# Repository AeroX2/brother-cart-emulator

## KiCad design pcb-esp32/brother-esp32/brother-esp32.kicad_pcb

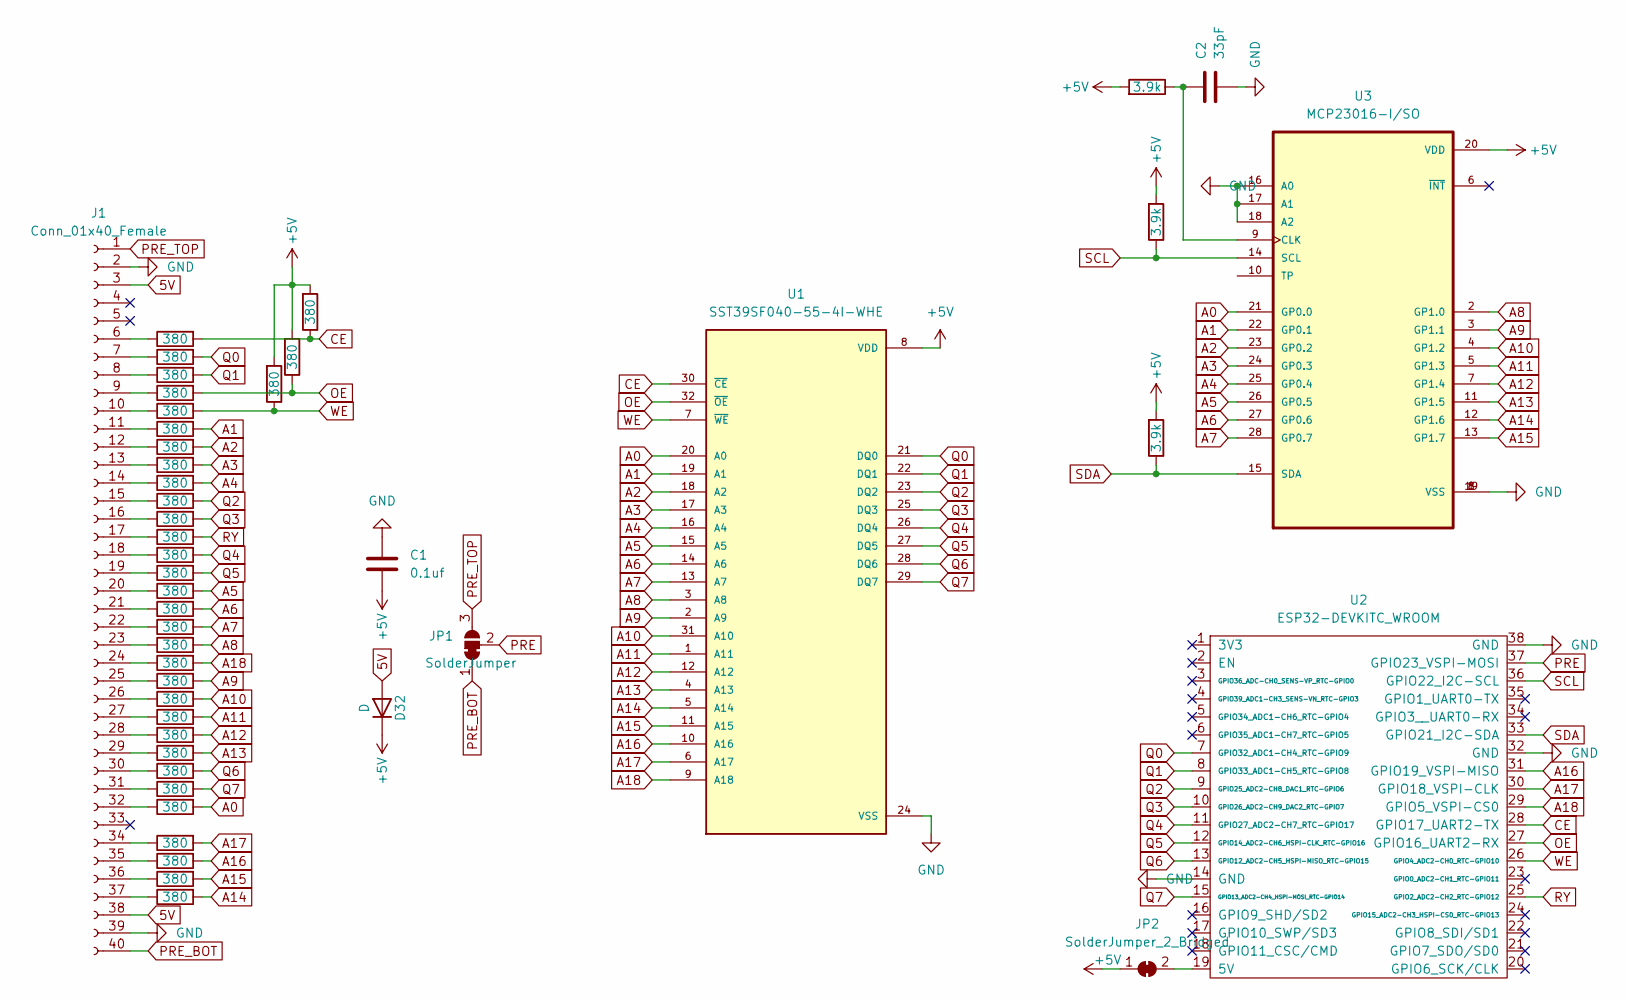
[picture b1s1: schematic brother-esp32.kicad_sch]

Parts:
C1: 0.1uf; C_0603_1608Metric_Pad1.08x0.95mm_HandSolder
C2: 33pF; C_0603_1608Metric_Pad1.08x0.95mm_HandSolder
D32: D; D_SOD-323_HandSoldering
J1: Conn_01x40_Female; PinHeader_1x40_SMD
JP1: SolderJumper; SolderJumper-3_P1.3mm_Bridged12_Pad1.0x1.5mm
JP2: SolderJumper_2_Bridged; SolderJumper-2_P1.3mm_Bridged_RoundedPad1.0x1.5mm
R1, R2, R3, R4, R5, R6, R7, R8, R9, R10, R11, R12, R13, R14, R15, R16, R17, R18, R19, R20, R21, R22, R23, R24, R25, R26, R27, R28, R29, R30, R31, R32, R33, R34: 380; R_0603_1608Metric_Pad0.98x0.95mm_HandSolder
R35, R36, R37: 3.9k; R_0603_1608Metric_Pad0.98x0.95mm_HandSolder
U1: SST39SF040-55-4I-WHE; SOP50P1400X120-32N; PARTREV C
U2: ESP32-DEVKITC_WROOM; ESP32-DOIT-DEVKIT
U3: MCP23016-I/SO; SOIC127P1030X265-28N

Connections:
5V: D32.2 (A), J1.3, J1.38
+5V: C1.2, D32.1 (K), JP2.1 (A), R32.2, R33.2, R34.2, R35.2, R36.2, R37.2, U1.8 (VDD), U3.20 (VDD)
A0: R27.2, U1.20 (A0), U3.21 (GP0.0)
A1: R6.2, U1.19 (A1), U3.22 (GP0.1)
A2: R7.2, U1.18 (A2), U3.23 (GP0.2)
A3: R8.2, U1.17 (A3), U3.24 (GP0.3)
A4: R9.2, U1.16 (A4), U3.25 (GP0.4)
A5: R15.2, U1.15 (A5), U3.26 (GP0.5)
A6: R16.2, U1.14 (A6), U3.27 (GP0.6)
A7: R17.2, U1.13 (A7), U3.28 (GP0.7)
A8: R18.2, U1.3 (A8), U3.2 (GP1.0)
A9: R20.2, U1.2 (A9), U3.3 (GP1.1)
A10: R21.2, U1.31 (A10), U3.4 (GP1.2)
A11: R22.2, U1.1 (A11), U3.5 (GP1.3)
A12: R23.2, U1.12 (A12), U3.7 (GP1.4)
A13: R24.2, U1.4 (A13), U3.11 (GP1.5)
A14: R31.2, U1.5 (A14), U3.12 (GP1.6)
A15: R30.2, U1.11 (A15), U3.13 (GP1.7)
A16: R29.2, U1.10 (A16), U2.31 (GPIO19_VSPI-MISO)
A17: R28.2, U1.6 (A17), U2.30 (GPIO18_VSPI-CLK)
A18: R19.2, U1.9 (A18), U2.29 (GPIO5_VSPI-CS0)
CE: R1.2, R34.1, U1.30 (~CE), U2.28 (GPIO17_UART2-TX)
GND: C1.1, C2.2, J1.2, J1.39, U1.24 (VSS), U2.14 (GND), U2.32 (GND), U2.38 (GND), U3.1 (VSS), U3.8 (VSS), U3.16 (A0), U3.17 (A1), U3.18 (A2), U3.19 (VSS)
unnamed: C2.1, R35.1, U3.9 (CLK)
unnamed: J1.6, R1.1
unnamed: J1.7, R2.1
unnamed: J1.8, R3.1
unnamed: J1.9, R4.1
unnamed: J1.10, R5.1
unnamed: J1.11, R6.1
unnamed: J1.12, R7.1
unnamed: J1.13, R8.1
unnamed: J1.14, R9.1
unnamed: J1.15, R10.1
unnamed: J1.16, R11.1
unnamed: J1.17, R12.1
unnamed: J1.18, R13.1
unnamed: J1.19, R14.1
unnamed: J1.20, R15.1
unnamed: J1.21, R16.1
unnamed: J1.22, R17.1
unnamed: J1.23, R18.1
unnamed: J1.24, R19.1
unnamed: J1.25, R20.1
unnamed: J1.26, R21.1
unnamed: J1.27, R22.1
unnamed: J1.28, R23.1
unnamed: J1.29, R24.1
unnamed: J1.30, R25.1
unnamed: J1.31, R26.1
unnamed: J1.32, R27.1
unnamed: J1.34, R28.1
unnamed: J1.35, R29.1
unnamed: J1.36, R30.1
unnamed: J1.37, R31.1
unnamed: JP2.2 (B), U2.19 (5V)
OE: R4.2, R33.1, U1.32 (~OE), U2.27 (GPIO16_UART2-RX)
PRE: JP1.2 (C), U2.37 (GPIO23_VSPI-MOSI)
PRE_BOT: J1.40, JP1.1 (A)
PRE_TOP: J1.1, JP1.3 (B)
Q0: R2.2, U1.21 (DQ0), U2.7 (GPIO32_ADC1-CH4_RTC-GPIO9)
Q1: R3.2, U1.22 (DQ1), U2.8 (GPIO33_ADC1-CH5_RTC-GPIO8)
Q2: R10.2, U1.23 (DQ2), U2.9 (GPIO25_ADC2-CH8_DAC1_RTC-GPIO6)
Q3: R11.2, U1.25 (DQ3), U2.10 (GPIO26_ADC2-CH9_DAC2_RTC-GPIO7)
Q4: R13.2, U1.26 (DQ4), U2.11 (GPIO27_ADC2-CH7_RTC-GPIO17)
Q5: R14.2, U1.27 (DQ5), U2.12 (GPIO14_ADC2-CH6_HSPI-CLK_RTC-GPIO16)
Q6: R25.2, U1.28 (DQ6), U2.13 (GPIO12_ADC2-CH5_HSPI-MISO_RTC-GPIO15)
Q7: R26.2, U1.29 (DQ7), U2.15 (GPIO13_ADC2-CH4_HSPI-MOSI_RTC-GPIO14)
RY: R12.2, U2.25 (GPIO2_ADC2-CH2_RTC-GPIO12)
SCL: R36.1, U2.36 (GPIO22_I2C-SCL), U3.14 (SCL)
SDA: R37.1, U2.33 (GPIO21_I2C-SDA), U3.15 (SDA)
WE: R5.2, R32.1, U1.7 (~WE), U2.26 (GPIO4_ADC2-CH0_RTC-GPIO10)

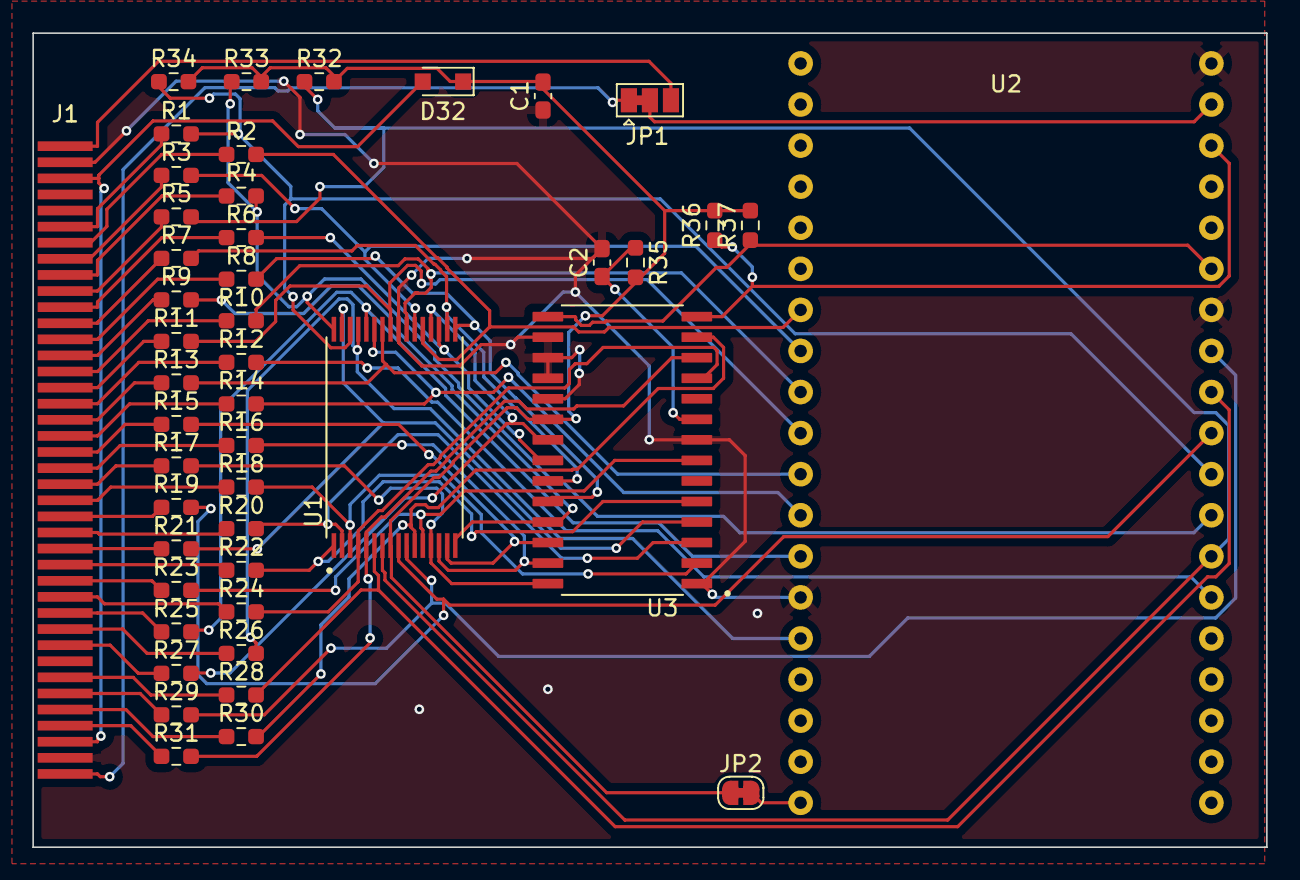
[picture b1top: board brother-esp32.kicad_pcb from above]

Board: 2 copper layers, 76.3 x 50.3 mm, 46 parts (0 on the bottom side), 72 nets.

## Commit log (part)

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2022-07-11 Convert to platformio
2022-09-04 Updated design remove diodes
2022-11-20 Add cracker.py
2022-12-31 Try and fix an issue with r2pipe
2023-03-07 Minor commit to explain the patches
2023-03-07 Fix picture links
2024-08-21 Really should migrate this script to something less volatile
2024-08-21 Imagine using lowercase for hex values, lol
2024-08-25 Add verbose output, add sanity check of binary blob, add comments to source code and also update README.md with known configurations
2024-08-26 Create LICENSE
2024-08-27 Show patch addresses in hex, dump CardIO imported functions
2024-09-01 Ignore .bin files
2024-09-01 Add command line options, add support for multiple card sizes (64/128/256 kiBytes), improve robustness and error reporting, update README.md
2024-10-06 Introduce dll_offset variable, fix card size choices, improve documentation, "make broth", update README.md
